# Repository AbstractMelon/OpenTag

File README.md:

# OpenTag
Open source lasertag / Base for Strikepoint Tag

## PCB Requirements
- Trigger
- IR Transmitter
- IR Receiver
- Sound System
- Lights
- Connection to headset
- Screen
- Action Changer
- Status LED's
- Reload input
## Headband PCB
- 6x IR Receiver

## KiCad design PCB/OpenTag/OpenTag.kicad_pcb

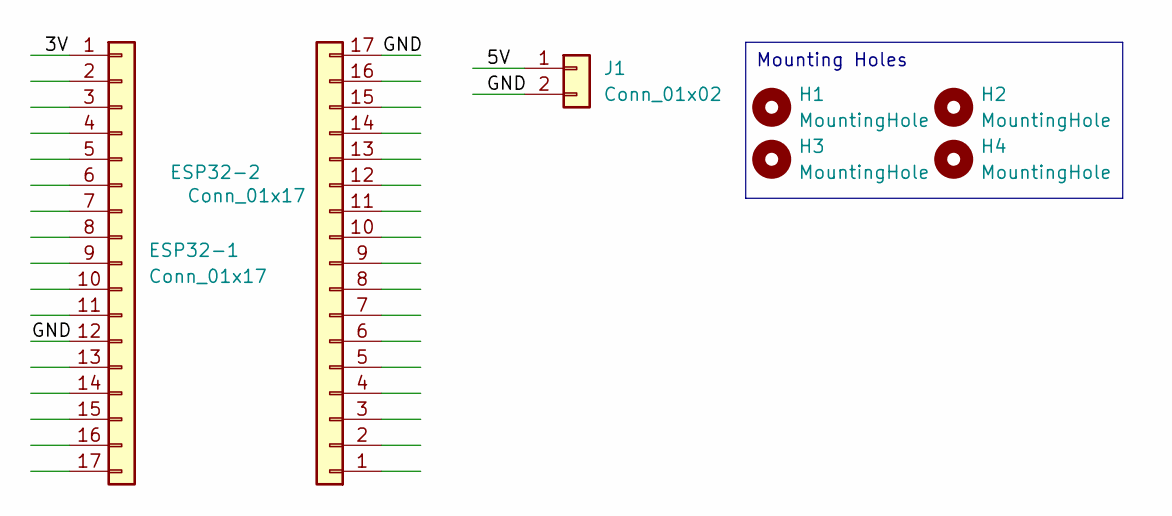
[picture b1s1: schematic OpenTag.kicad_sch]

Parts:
ESP32-1, ESP32-2: Conn_01x17; PinSocket_1x17_P2.54mm_Vertical
H1, H2, H3, H4: MountingHole; MountingHole_3.2mm_M3
J1: Conn_01x02; JST_EH_B2B-EH-A_1x02_P2.50mm_Vertical

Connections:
/3V: ESP32-1.1
/5V: ESP32-1.17, J1.1
/GND: ESP32-1.12, ESP32-2.17 (Pin_17_17), J1.2

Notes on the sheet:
Mounting Holes

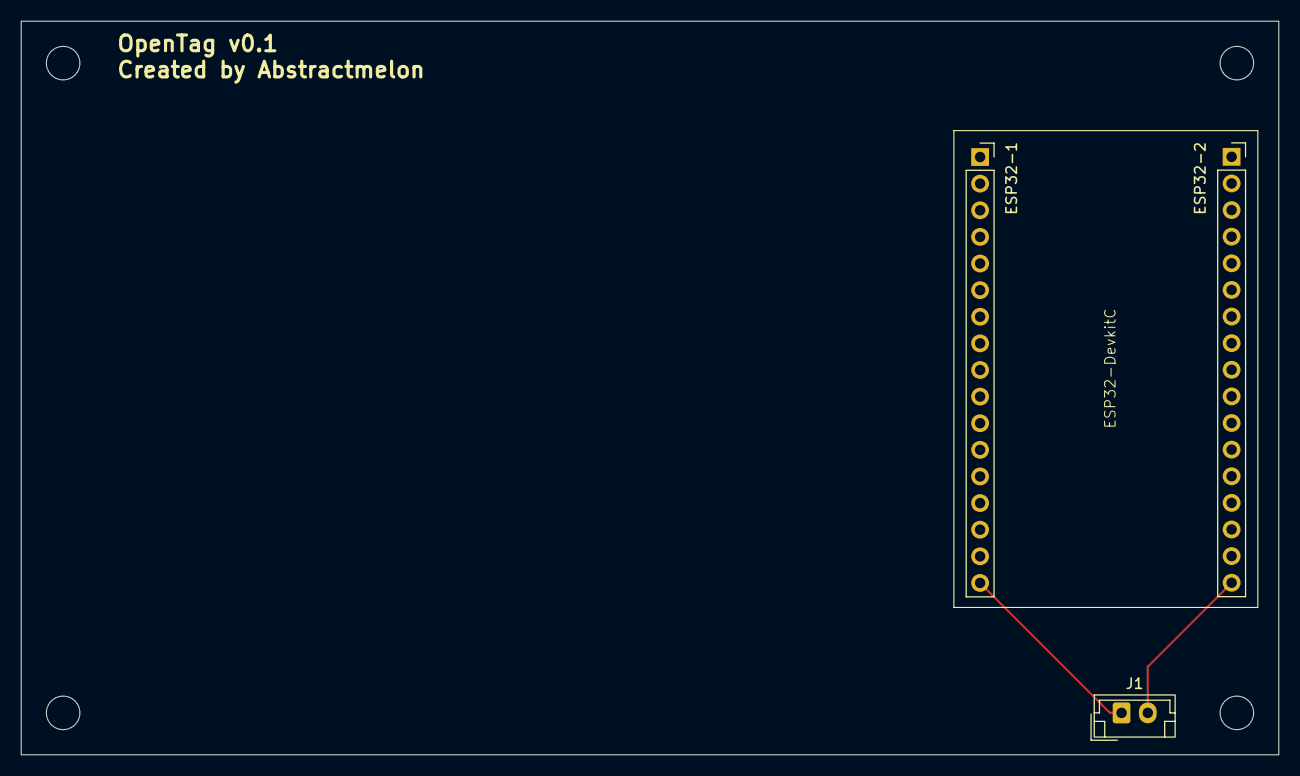
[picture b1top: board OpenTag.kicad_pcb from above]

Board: 2 copper layers, 120.0 x 70.0 mm, 7 parts (0 on the bottom side), 2 nets.

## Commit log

2026-05-04 Push PCB
2026-05-05 Add .gitignore to exclude PCB/OpenTag/.history directory
2026-05-05 Add initial Shopping List document
2026-05-05 Add PlatformIO project files
2026-05-05 Base ESP32 script
2026-05-06 Update PCB
2026-05-06 Update ESP32 script structure and update .gitignore for backup files
2026-05-06 Base client/server
2026-05-06 Base connection system
2026-05-08 Update to blink LED
2026-05-14 Update script
